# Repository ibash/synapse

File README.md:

# Synapse

A Neuron alternative for the Dygma Raise that uses an STM32 Blackpill.
[ref](https://github.com/qmk/qmk_firmware/pull/13543)

## Generating production files

See [jlcpcb](https://support.jlcpcb.com/article/149-how-to-generate-gerber-and-drill-files-in-kicad).

## Parts
- USB-C Connectors: Korean Hroparts Elec TYPE-C-31-M-12
- 2.7k Resistors: UNI-ROYAL(Uniroyal Elec) 1206W4F2701T5E
- 200k Resistors: UNI-ROYAL(Uniroyal Elec) 1206W4F2003T5E

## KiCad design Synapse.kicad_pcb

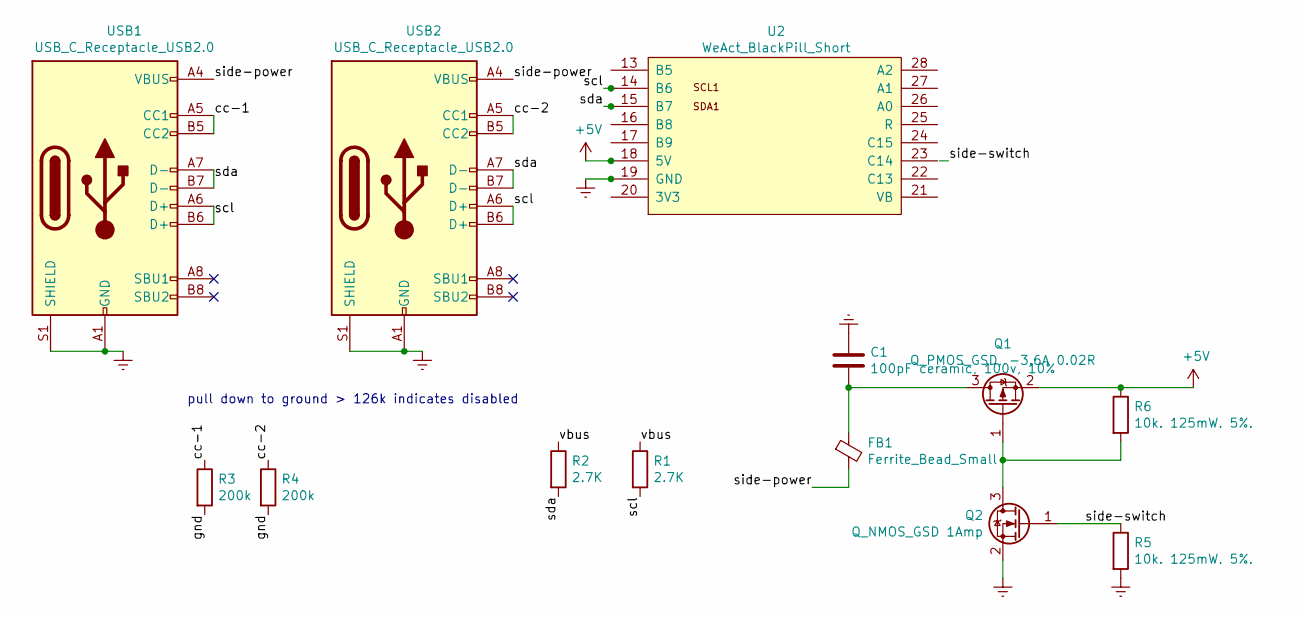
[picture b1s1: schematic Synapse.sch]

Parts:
C1: 100pF ceramic, 100v, 10%; C_0805_2012Metric; LCSC C159771
FB1: Ferrite_Bead_Small; L_0805_2012Metric; LCSC C1017
Q1: Q_PMOS_GSD, -3.6A 0.02R; SOT-23; LCSC C15127
Q2: Q_NMOS_GSD 1Amp; SOT-23; LCSC C20917
R1, R2: 2.7K; R_0805_2012Metric; LCSC C17530
R3, R4: 200k; R_0805_2012Metric; LCSC C17539
R5, R6: 10k. 125mW. 5%.; R_0805_2012Metric; LCSC C17414
U2: WeAct_BlackPill_Short; BlackPill_Short
USB1, USB2: USB_C_Receptacle_USB2.0; USB_C_Receptacle_HRO_TYPE-C-31-M-12; LCSC C165948

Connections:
+5V: Q1.2 (S), R6.1, U2.18 (5V)
/cc-1: R3.1, USB1.A5 (CC1), USB1.B5 (CC2)
/cc-2: R4.1, USB2.A5 (CC1), USB2.B5 (CC2)
/gnd: R3.2, R4.2
/scl: R1.2, U2.14 (B6), USB1.A6 (D+), USB1.B6 (D+), USB2.A6 (D+), USB2.B6 (D+)
/sda: R2.2, U2.15 (B7), USB1.A7 (D-), USB1.B7 (D-), USB2.A7 (D-), USB2.B7 (D-)
/side-power: FB1.2, USB1.A4 (VBUS), USB1.A9 (VBUS), USB1.B4 (VBUS), USB1.B9 (VBUS), USB2.A4 (VBUS), USB2.A9 (VBUS), USB2.B4 (VBUS), USB2.B9 (VBUS)
/side-switch: Q2.1 (G), R5.1
/vbus: R1.1, R2.1
GNDREF: C1.1, Q2.2 (S), R5.2, U2.19 (GND), USB1.A1 (GND), USB1.A12 (GND), USB1.B1 (GND), USB1.B12 (GND), USB1.S1 (SHIELD), USB2.A1 (GND), USB2.A12 (GND), USB2.B1 (GND), USB2.B12 (GND), USB2.S1 (SHIELD)
unnamed: C1.2, FB1.1, Q1.3 (D)
unnamed: Q1.1 (G), Q2.3 (D), R6.2

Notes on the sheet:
pull down to ground > 126k indicates disabled

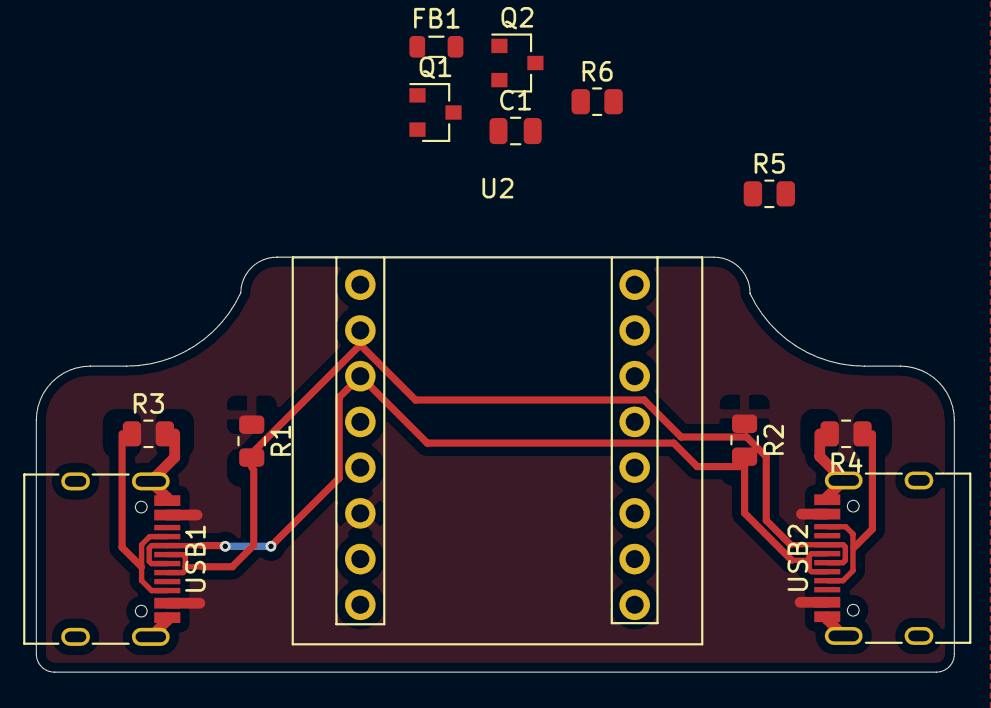
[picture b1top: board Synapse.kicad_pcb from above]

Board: 2 copper layers, 51.0 x 23.1 mm, 13 parts (0 on the bottom side), 12 nets.

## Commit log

2021-07-14 Rebuild the pcb in a cleaner way
2021-07-14 Use VCC for a top layer
2021-07-14 synapse mini
2021-07-14 PAUSED: Use `git resume` to continue working.
